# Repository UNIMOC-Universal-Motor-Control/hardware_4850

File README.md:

# hardware_4850
48V at 50A with optimised colling

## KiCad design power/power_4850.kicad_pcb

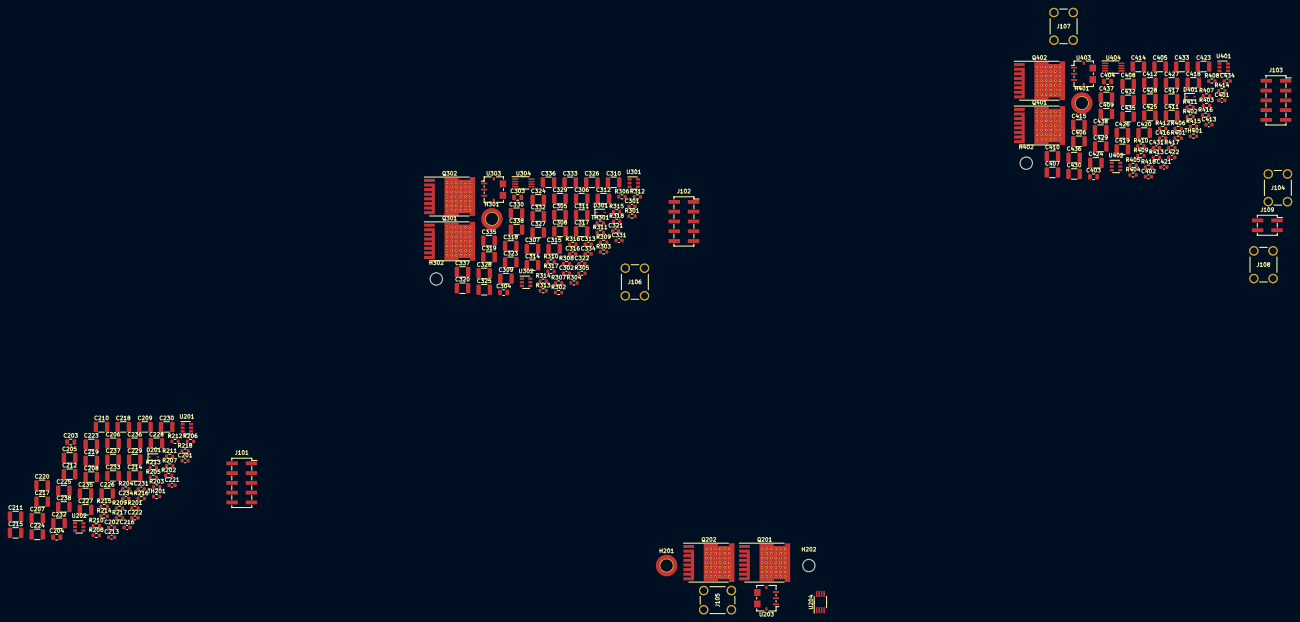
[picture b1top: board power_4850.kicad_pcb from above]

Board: 4 copper layers, 207 parts (0 on the bottom side), 92 nets, no tracks yet.

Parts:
C201, C202, C213, C216, C231, C234, C301, C302, C313, C316, C331, C334, C401, C402, C413, C416, C431, C434: 100n; C_0603_1608Metric
C203, C204, C303, C304, C403, C404: 10u; C_0805_2012Metric
C205, C206, C207, C208, C209, C210, C211, C212, C214, C215, C217, C218, C219, C220, C223, C224, C225, C226, C227, C228, C229, C230, C232, C233, C235, C236, C237, C238, C305, C306, C307, C308, C309, C310, C311, C312, C314, C315, C317, C318, C319, C320, C323, C324, C325, C326, C327, C328, C329, C330, C332, C333, C335, C336, C337, C338, C405, C406, C407, C408, C409, C410, C411, C412, C414, C415, C417, C418, C419, C420, C423, C424, C425, C426, C427, C428, C429, C430, C432, C433, C435, C436, C437, C438: 4u7; C_1210_3225Metric
C221, C222, C321, C322, C421, C422: DNP; C_0603_1608Metric
D201, D301, D401: 1N4148WS; D_SOD-323
H201, H301, H401: GND; MountingHole_3.2mm_M3_DIN965_Pad_TopOnly
H202, H302, H402: Phase; MountingHole_3.2mm_M3
J101: PA; PinSocket_2x05_P2.54mm_Vertical_SMD
J102: PB; PinSocket_2x05_P2.54mm_Vertical_SMD
J103: PC; PinSocket_2x05_P2.54mm_Vertical_SMD
J104: +; 8X8X8.4MM TERMINAL
J105: A; 8X8X8.4MM TERMINAL
J106: B; 8X8X8.4MM TERMINAL
J107: C; 8X8X8.4MM TERMINAL
J108: GND; 8X8X8.4MM TERMINAL
J109: Supply; PinSocket_2x02_P2.54mm_Vertical_SMD
Q201, Q202, Q301, Q302, Q401, Q402: IPT015N10N5; Infineon_PG-HSOF-8-1_ThermalVias
R201, R202, R203, R204, R211, R301, R302, R303, R304, R311, R401, R402, R403, R404, R411: 33k; R_0603_1608Metric
R205, R206, R207, R208, R305, R306, R307, R308, R405, R406, R407, R408: 1R; R_0603_1608Metric
R209, R210, R309, R310, R409, R410: 10R; R_0603_1608Metric
R212, R213, R214, R312, R313, R314, R412, R413, R414: 1k; R_0603_1608Metric
R215, R216, R315, R316, R415, R416: 4k7; R_0603_1608Metric
R217, R218, R317, R318, R417, R418: 10k; R_0603_1608Metric
TH201, TH301, TH401: NTC 10k; R_0603_1608Metric
U201, U202, U301, U302, U401, U402: 1EDN7550B; SOT-23-6
U203, U303, U403: ACS72981KLATR-150B5; Allegro_PSOF-7_4.8x6.4mm_P1.60mm
U204, U304, U404: MCP6D11-EMS; MSOP-8_3x3mm_P0.65mm

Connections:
+BATT: C205.1, C206.1, C207.1, C208.1, C209.1, C210.1, C211.1, C212.1, C214.1, C215.1, C217.1, C218.1, C219.1, C220.1, C223.1, C224.1, C225.1, C226.1, C227.1, C228.1, C229.1, C230.1, C232.1, C233.1, C235.1, C236.1, C237.1, C238.1, C305.1, C306.1, C307.1, C308.1, C309.1, C310.1, C311.1, C312.1, C314.1, C315.1, C317.1, C318.1, C319.1, C320.1, C323.1, C324.1, C325.1, C326.1, C327.1, C328.1, C329.1, C330.1, C332.1, C333.1, C335.1, C336.1, C337.1, C338.1, C405.1, C406.1, C407.1, C408.1, C409.1, C410.1, C411.1, C412.1, C414.1, C415.1, C417.1, C418.1, C419.1, C420.1, C423.1, C424.1, C425.1, C426.1, C427.1, C428.1, C429.1, C430.1, C432.1, C433.1, C435.1, C436.1, C437.1, C438.1, J104.1, J109.2, J109.4, Q201.3, Q301.3, Q401.3
/phase_a/+5V: C213.1, C231.1, J101.4, R213.1, U203.1, U204.3, U204.7
/phase_a/+12V: D201.2, J101.2, R210.2
/phase_a/GNDA: C213.2, C216.2, C231.2, C234.2, J101.6, R212.2, R214.2, U203.2, U203.4, U203.7, U204.6
/phase_a/I+: C222.1, J101.8, R218.1, U204.4
/phase_a/I-: C221.1, J101.10, R217.1, U204.5
/phase_a/Phase+: C201.2, C203.2, Q201.2, Q202.3, R211.1, U201.2, U203.5
/phase_a/Phase-: J105.1, U203.6
/phase_a/PwmH: J101.3, R201.2, R204.2
/phase_a/PwmL: J101.1, R202.2, R203.2
/phase_a/T+: J101.9, TH201.1
/phase_a/T-: J101.7, TH201.2
/phase_a/V: J101.5, R211.2, R212.1
/phase_b/+5V: C313.1, C331.1, J102.4, R313.1, U303.1, U304.3, U304.7
/phase_b/+12V: D301.2, J102.2, R310.2
/phase_b/GNDA: C313.2, C316.2, C331.2, C334.2, J102.6, R312.2, R314.2, U303.2, U303.4, U303.7, U304.6
/phase_b/I+: C322.1, J102.8, R318.1, U304.4
/phase_b/I-: C321.1, J102.10, R317.1, U304.5
/phase_b/Phase+: C301.2, C303.2, Q301.2, Q302.3, R311.1, U301.2, U303.5
/phase_b/Phase-: J106.1, U303.6
/phase_b/PwmH: J102.3, R301.2, R304.2
/phase_b/PwmL: J102.1, R302.2, R303.2
/phase_b/T+: J102.9, TH301.1
/phase_b/T-: J102.7, TH301.2
/phase_b/V: J102.5, R311.2, R312.1
/phase_c/+5V: C413.1, C431.1, J103.4, R413.1, U403.1, U404.3, U404.7
/phase_c/+12V: D401.2, J103.2, R410.2
/phase_c/GNDA: C413.2, C416.2, C431.2, C434.2, J103.6, R412.2, R414.2, U403.2, U403.4, U403.7, U404.6
/phase_c/I+: C422.1, J103.8, R418.1, U404.4
/phase_c/I-: C421.1, J103.10, R417.1, U404.5
/phase_c/Phase+: C401.2, C403.2, Q401.2, Q402.3, R411.1, U401.2, U403.5
/phase_c/Phase-: J107.1, U403.6
/phase_c/PwmH: J103.3, R401.2, R404.2
/phase_c/PwmL: J103.1, R402.2, R403.2
/phase_c/T+: J103.9, TH401.1
/phase_c/T-: J103.7, TH401.2
/phase_c/V: J103.5, R411.2, R412.1
GNDPWR: C202.2, C204.2, C205.2, C206.2, C207.2, C208.2, C209.2, C210.2, C211.2, C212.2, C214.2, C215.2, C217.2, C218.2, C219.2, C220.2, C223.2, C224.2, C225.2, C226.2, C227.2, C228.2, C229.2, C230.2, C232.2, C233.2, C235.2, C236.2, C237.2, C238.2, C302.2, C304.2, C305.2, C306.2, C307.2, C308.2, C309.2, C310.2, C311.2, C312.2, C314.2, C315.2, C317.2, C318.2, C319.2, C320.2, C323.2, C324.2, C325.2, C326.2, C327.2, C328.2, C329.2, C330.2, C332.2, C333.2, C335.2, C336.2, C337.2, C338.2, C402.2, C404.2, C405.2, C406.2, C407.2, C408.2, C409.2, C410.2, C411.2, C412.2, C414.2, C415.2, C417.2, C418.2, C419.2, C420.2, C423.2, C424.2, C425.2, C426.2, C427.2, C428.2, C429.2, C430.2, C432.2, C433.2, C435.2, C436.2, C437.2, C438.2, H201.1, H301.1, H401.1, J108.1, J109.1, J109.3, Q202.2, Q302.2, Q402.2, U202.2, U302.2, U402.2
unnamed: C201.1, C203.1, R209.1, U201.4
unnamed: C202.1, C204.1, R210.1, U202.4
unnamed: C216.1, R213.2, R214.1, R216.2
unnamed: C221.2, R215.1, R217.2, U204.8
unnamed: C222.2, R216.1, R218.2, U204.1
unnamed: C234.1, U204.2
unnamed: C301.1, C303.1, R309.1, U301.4
unnamed: C302.1, C304.1, R310.1, U302.4
unnamed: C316.1, R313.2, R314.1, R316.2
unnamed: C321.2, R315.1, R317.2, U304.8
unnamed: C322.2, R316.1, R318.2, U304.1
unnamed: C334.1, U304.2
unnamed: C401.1, C403.1, R409.1, U401.4
unnamed: C402.1, C404.1, R410.1, U402.4
unnamed: C416.1, R413.2, R414.1, R416.2
unnamed: C421.2, R415.1, R417.2, U404.8
unnamed: C422.2, R416.1, R418.2, U404.1
unnamed: C434.1, U404.2
unnamed: D201.1, R209.2
unnamed: D301.1, R309.2
unnamed: D401.1, R409.2
unnamed: Q201.1, R205.1, R206.1
unnamed: Q202.1, R207.1, R208.1
unnamed: Q301.1, R305.1, R306.1
unnamed: Q302.1, R307.1, R308.1
unnamed: Q401.1, R405.1, R406.1
unnamed: Q402.1, R407.1, R408.1
unnamed: R201.1, U201.3
unnamed: R202.1, U201.1
unnamed: R203.1, U202.3
unnamed: R204.1, U202.1
unnamed: R205.2, U201.5
unnamed: R206.2, U201.6
unnamed: R207.2, U202.5
unnamed: R208.2, U202.6
unnamed: R215.2, U203.3
unnamed: R301.1, U301.3
unnamed: R302.1, U301.1
unnamed: R303.1, U302.3
unnamed: R304.1, U302.1
unnamed: R305.2, U301.5
unnamed: R306.2, U301.6
unnamed: R307.2, U302.5
unnamed: R308.2, U302.6
unnamed: R315.2, U303.3
unnamed: R401.1, U401.3
unnamed: R402.1, U401.1
unnamed: R403.1, U402.3
unnamed: R404.1, U402.1
unnamed: R405.2, U401.5
unnamed: R406.2, U401.6
unnamed: R407.2, U402.5
unnamed: R408.2, U402.6
unnamed: R415.2, U403.3

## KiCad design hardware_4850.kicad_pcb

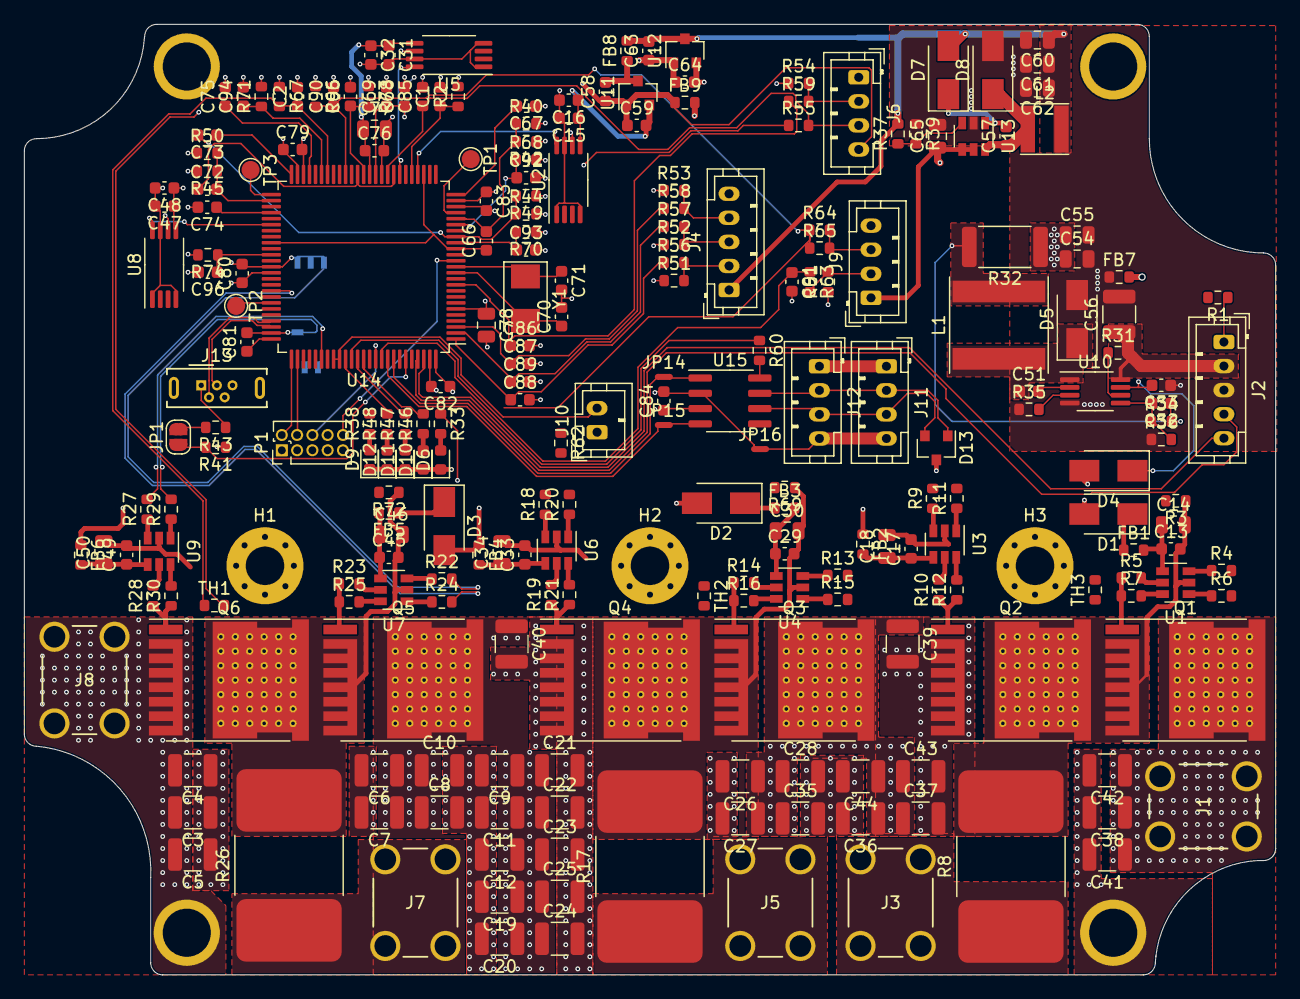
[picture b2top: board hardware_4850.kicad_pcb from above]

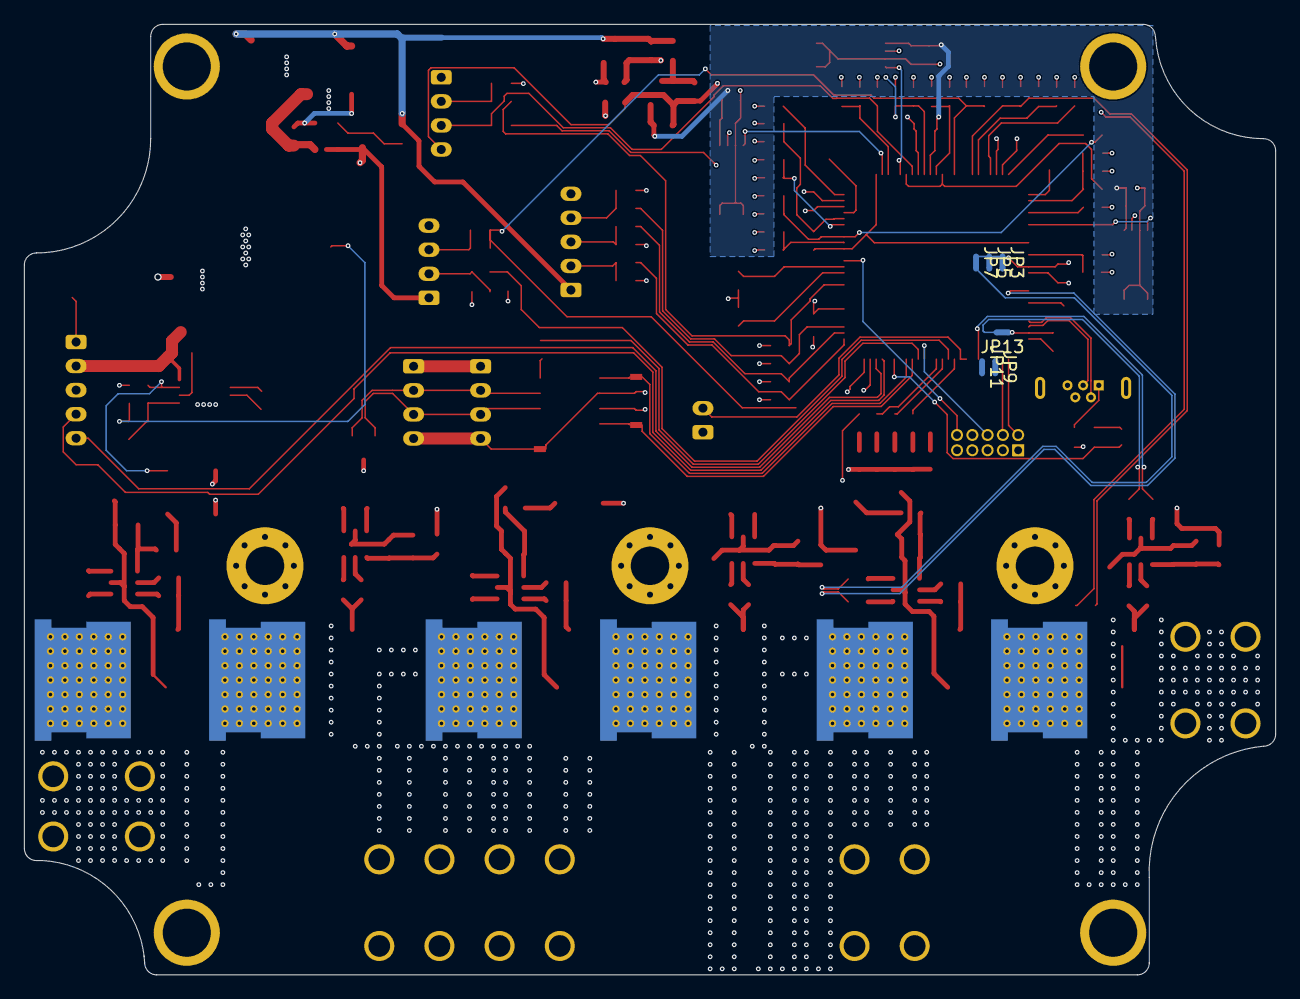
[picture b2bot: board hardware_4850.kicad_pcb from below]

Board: 4 copper layers, 104.0 x 79.0 mm, 250 parts (6 on the bottom side), 146 nets.

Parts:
C1, C2, C13, C16, C17, C29, C32, C33, C45, C48, C49, C51, C57, C67, C68, C74, C75, C76, C79, C80, C81, C82, C83, C84, C85, C92, C93, C94, C95, C96: 100n; C_0603_1608Metric
C3, C4, C5, C6, C7, C8, C9, C10, C11, C12, C19, C20, C21, C22, C23, C24, C25, C26, C27, C28, C35, C36, C37, C38, C39, C40, C41, C42, C43, C44, C56: 4u7; C_1210_3225Metric
C14, C18, C30, C34, C46, C50, C54, C55, C60, C61, C62, C65, C77, C78: 10u; C_0805_2012Metric
C15, C31, C47, C66, C72, C73: 10n; C_0603_1608Metric
C52, C86, C87, C88, C89, C90, C91: 2n2; C_0603_1608Metric
C53, C58, C59, C63, C64, C69: 1u; C_0603_1608Metric
C70, C71: 15p; C_0603_1608Metric
D1, D2, D3, D4, D5, D7, D8: SS210; D_SMA
D6: 12V; LED_0603_1608Metric
D9: 3V3; LED_0603_1608Metric
D10: RUN; LED_0603_1608Metric
D11: ERROR; LED_0603_1608Metric
D12: PWM; LED_0603_1608Metric
D13: ESDCAN24-2BLY; SOT-23
FB1, FB2, FB3, FB4, FB5, FB6, FB7, FB8, FB9: BLM18PG221SN1D; R_0603_1608Metric
H1, H2, H3: MountingHole_Pad; MountingHole_3.2mm_M3_Pad_Via
J1: +; 8X8X8.4MM TERMINAL
J2: Display; JST_PH_B5B-PH-K_1x05_P2.00mm_Vertical
J3: A; 8X8X8.4MM TERMINAL
J4: HALL; JST_PH_B5B-PH-K_1x05_P2.00mm_Vertical
J5: B; 8X8X8.4MM TERMINAL
J6: MOT_AUX; JST_PH_B4B-PH-K_1x04_P2.00mm_Vertical
J7: C; 8X8X8.4MM TERMINAL
J8: GND; 8X8X8.4MM TERMINAL
J9: CRANK; JST_PH_B4B-PH-K_1x04_P2.00mm_Vertical
J10: Enable; JST_PH_B2B-PH-K_1x02_P2.00mm_Vertical
J11: CAN_IN; JST_PH_B4B-PH-K_1x04_P2.00mm_Vertical
J12: CAN_OUT; JST_PH_B4B-PH-K_1x04_P2.00mm_Vertical
J13: Debug; USB_Micro-B_Wuerth_614105150721_Vertical
JP1: BTLDR; SolderJumper-2_P1.3mm_Open_RoundedPad1.0x1.5mm
JP3: PA-; NetTie-2_SMD_Pad0.5mm
JP5: PB-; NetTie-2_SMD_Pad0.5mm
JP7: PC-; NetTie-2_SMD_Pad0.5mm
JP9: PAN-; NetTie-2_SMD_Pad0.5mm
JP11: PBN-; NetTie-2_SMD_Pad0.5mm
JP13: PCN-; NetTie-2_SMD_Pad0.5mm
JP14: CAN_TX; NetTie-2_SMD_Pad0.5mm
JP15: CAN_RX; NetTie-2_SMD_Pad0.5mm
JP16: CAN_GND; NetTie-2_SMD_Pad0.5mm
L1: 330u; L_Taiyo-Yuden_NR-80xx
L2: 10u; L_Taiyo-Yuden_NR-40xx
N1: Housing; RND-455-00370
P1: SWD; PinHeader_2x05_P1.27mm_Vertical
Q1, Q2, Q3, Q4, Q5, Q6: IPT015N10N5; Infineon_PG-HSOF-8-1_ThermalVias
R1, R3, R4, R6, R9, R11, R13, R15, R18, R20, R22, R24, R27, R29, R69, R72: 33k; R_0603_1608Metric
R2, R40, R42, R44, R45, R49, R50, R51, R52, R53, R54, R61, R62, R68, R71, R74: 1k; R_0603_1608Metric
R5, R7, R10, R12, R14, R16, R19, R21, R23, R25, R28, R30: 1R; R_0603_1608Metric
R8, R17, R26: R0002; R_5930_15076Metric_Pad5.20x8.75mm
R31: 220k; R_0603_1608Metric
R32: 2R2; R_2512_6332Metric
R33, R36, R43, R56, R57, R58, R59, R63, R64, R65, R66: 3k3; R_0603_1608Metric
R34, R39, R41, R55, R60, R67, R70, R73: 10k; R_0603_1608Metric
R35: 100k; R_0603_1608Metric
R37: 56k; R_0603_1608Metric
R38, R46, R47, R48: 470R; R_0603_1608Metric
TH1, TH2, TH3: NTC 10k; R_0603_1608Metric
TP1: IA_AC; TestPoint_Pad_D1.5mm
TP2: IC_AC; TestPoint_Pad_D1.5mm
TP3: IB_AC; TestPoint_Pad_D1.5mm
U1, U3, U4, U6, U7, U9: 1EDN7550B; SOT-23-6
U2, U5, U8: INA240A2PWR; TSSOP-8_4.4x3mm_P0.65mm
U10: LM5008; MSOP-8_3x3mm_P0.65mm
U11, U12: XC6206P332MR; SOT-23
U13: LMR12010X; SOT-23-6
U14: STM32G473VCTx; LQFP-100_14x14mm_P0.5mm
U15: SN65HVD230; SOIC-8_3.9x4.9mm_P1.27mm
Y1: 8MHz; Crystal_SMD_5032-2Pin_5.0x3.2mm

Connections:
+3.3VADC: C15.1, C16.1, C31.1, C32.1, C47.1, C48.1, C59.2, C76.1, C77.1, U2.5, U5.5, U8.5, U11.2, U14.37
+3V3: C64.2, C78.1, C79.1, C80.1, C81.1, C82.1, C83.1, C84.1, P1.1, R38.2, R51.1, R52.1, R53.1, R54.1, R61.1, R62.2, U12.2, U14.6, U14.24, U14.49, U14.64, U14.75, U14.100, U15.3
+5V: C60.1, C61.1, C62.1, C63.2, D7.2, FB8.2, J4.1, L2.2, R37.2, U12.3
+12V: C54.1, C55.1, C65.1, D1.2, D2.2, D3.2, D4.2, FB2.1, FB4.1, FB6.1, J9.1, R32.1, R33.1, U13.4, U13.5
+BATT: C3.1, C4.1, C5.1, C6.1, C7.1, C8.1, C9.1, C10.1, C11.1, C12.1, C19.1, C20.1, C21.1, C22.1, C23.1, C24.1, C25.1, C26.1, C27.1, C28.1, C35.1, C36.1, C37.1, C38.1, C39.1, C40.1, C41.1, C42.1, C43.1, C44.1, J1.1, J2.1, Q1.3, Q3.3, Q5.3, R1.1
/Interface/CAN+: D13.1, J11.2, J12.2, U15.7
/Interface/CAN-: D13.2, J11.3, J12.3, U15.6
/Interface/CAN_GND: J11.4, J12.4, JP16.2
/Interface/CAN_RX: JP15.1, U14.92
/Interface/CAN_SLP: R60.1, U14.91
/Interface/CAN_TX: JP14.1, U14.93
/Interface/ENABLE+: J10.1, R62.1
/Interface/ENABLE-: J10.2, U14.83, U14.84
/Interface/HALL_A: C88.1, R56.1, U14.1
/Interface/HALL_A_IN: J4.2, R51.2, R56.2
/Interface/HALL_B: C89.1, R57.1, U14.2
/Interface/HALL_B_IN: J4.3, R52.2, R57.2
/Interface/HALL_C: C87.1, R58.1, U14.3
/Interface/HALL_C_IN: J4.4, R53.2, R58.2
/Interface/PULSE_CRK: C91.1, R63.1, U14.86
/Interface/PULSE_CRK_IN: J9.2, R61.2, R63.2
/Interface/PULSE_MOT: C86.1, R59.1, U14.10
/Interface/PULSE_MOT_IN: J6.2, R54.2, R59.2
/Interface/TORQ_CRK_IN: J9.3, R64.2, R65.2
/Interface/VREF: C68.1, C69.1, R40.2, R44.2, R45.2, R55.1, R67.1, R70.1, R73.1, U2.6, U5.6, U8.6, U14.36
/mcu/AIN_CRK_TORQ: C90.1, R64.1, R65.1, R66.2, U14.41
/mcu/AIN_IA: U2.8, U14.29
/mcu/AIN_IB: U5.8, U14.32
/mcu/AIN_IC: U8.8, U14.56
/mcu/AIN_TEMP_A: C2.1, R67.2, TH1.1, U14.44
/mcu/AIN_TEMP_B: C93.1, R70.2, TH2.1, U14.17
/mcu/AIN_TEMP_C: C95.1, R73.2, TH3.1, U14.38
/mcu/AIN_TEMP_MOT: C85.1, J6.3, R55.2, U14.34
/mcu/AIN_VA: C92.1, R3.2, R68.1, U14.20
/mcu/AIN_VB: C94.1, R69.2, R71.1, U14.45
/mcu/AIN_VC: C96.1, R72.2, R74.1, U14.61
/mcu/AIN_VDC: C1.1, R1.2, R2.1, U14.30
/mcu/DISP_RX: J2.5, U14.98
/mcu/DISP_TX: J2.4, U14.97
/mcu/IA_AC: TP1.1, U14.22
/mcu/IA_AC_BIAS: C67.2, U14.25
/mcu/IA_AC_IN: C66.2, R40.1, R42.2, U14.21
/mcu/IA_DC: C66.1, U14.16, U14.28, U14.59
/mcu/IB_AC: TP3.1, U14.51
/mcu/IB_AC_BIAS: C75.1, U14.47
/mcu/IB_AC_IN: C72.2, R45.1, R50.2, U14.52
/mcu/IB_DC: C72.1, U14.33, U14.39
/mcu/IC_AC: TP2.1, U14.69
/mcu/IC_AC_BIAS: C74.1, U14.54
/mcu/IC_AC_IN: C73.2, R44.1, R49.2, U14.18
/mcu/IC_DC: C73.1, U14.50
/mcu/NRST: P1.10, U14.14
/mcu/PWM_A+: R6.2, U14.65
/mcu/PWM_A-: JP3.2, R4.2
/mcu/PWM_AN+: R9.2, U14.79
/mcu/PWM_AN-: JP9.2, R11.2
/mcu/PWM_B+: R15.2, U14.66
/mcu/PWM_B-: JP5.2, R13.2
/mcu/PWM_BN+: R18.2, U14.80
/mcu/PWM_BN-: JP11.2, R20.2
/mcu/PWM_C+: R24.2, U14.67
/mcu/PWM_C-: JP7.2, R22.2
/mcu/PWM_CN+: R27.2, U14.81
/mcu/PWM_CN-: JP13.2, R29.2
/mcu/SWD_CLK: P1.4, U14.77
/mcu/SWD_IO: P1.2, U14.76
/mcu/SWD_SWO: P1.6, U14.90
/mcu/USB_D+: J13.3, U14.73
/mcu/USB_D-: J13.2, U14.72
/mcu/USB_VBUS: JP1.2, R43.2
/phase_a/Phase+: J3.1, R8.1, U2.2
/phase_a/Phase-: C13.2, C14.2, Q1.2, Q2.3, R3.1, R8.2, U1.2, U2.3
/phase_b/Phase+: J5.1, R17.1, U5.2
/phase_b/Phase-: C29.2, C30.2, Q3.2, Q4.3, R17.2, R69.1, U4.2, U5.3
/phase_c/Phase+: J7.1, R26.1, U8.2
/phase_c/Phase-: C45.2, C46.2, Q5.2, Q6.3, R26.2, R72.1, U7.2, U8.3
/power_supply/DCDC_VIN: C56.1, J2.2, R31.2, U10.8
GNDA: C1.2, C2.2, C15.2, C16.2, C31.2, C32.2, C47.2, C48.2, C58.1, C59.1, C67.1, C68.2, C69.2, C74.2, C75.2, C76.2, C77.2, C85.2, C90.2, C92.2, C93.2, C94.2, C95.2, C96.2, FB9.1, J6.4, R2.2, R42.1, R49.1, R50.1, R66.1, R68.2, R71.2, R74.2, TH1.2, TH2.2, TH3.2, U2.1, U2.4, U2.7, U5.1, U5.4, U5.7, U8.1, U8.4, U8.7, U11.1, U14.35
GNDD: C53.1, C54.2, C55.2, C56.2, C60.2, C61.2, C62.2, C63.1, C64.1, C65.2, C70.2, C71.2, C78.2, C79.2, C80.2, C81.2, C82.2, C83.2, C84.2, C86.2, C87.2, C88.2, C89.2, C91.2, D5.2, D6.1, D8.2, D9.1, D10.1, D11.1, D12.1, D13.3, FB7.1, FB9.2, J2.3, J4.5, J6.1, J9.4, J13.5, J13.6, JP3.1, JP5.1, JP7.1, JP9.1, JP11.1, JP13.1, JP16.1, P1.3, P1.5, R35.1, R36.1, R39.1, R41.1, U10.4, U12.1, U13.2, U14.23, U14.48, U14.63, U14.74, U14.99, U15.2
GNDPWR: C3.2, C4.2, C5.2, C6.2, C7.2, C8.2, C9.2, C10.2, C11.2, C12.2, C17.2, C18.2, C19.2, C20.2, C21.2, C22.2, C23.2, C24.2, C25.2, C26.2, C27.2, C28.2, C33.2, C34.2, C35.2, C36.2, C37.2, C38.2, C39.2, C40.2, C41.2, C42.2, C43.2, C44.2, C49.2, C50.2, FB7.2, H1.1, H2.1, H3.1, J8.1, N1.1, Q2.2, Q4.2, Q6.2, U3.2, U6.2, U9.2
unnamed: C13.1, C14.1, FB1.2, U1.4
unnamed: C17.1, C18.1, FB2.2, U3.4
unnamed: C29.1, C30.1, FB3.2, U4.4
unnamed: C33.1, C34.1, FB4.2, U6.4
unnamed: C45.1, C46.1, FB5.2, U7.4
unnamed: C49.1, C50.1, FB6.2, U9.4
unnamed: C51.1, D5.1, L1.1, U10.1
unnamed: C51.2, U10.2
unnamed: C52.1, L1.2, R32.2, R34.2
unnamed: C52.2, R34.1, R36.2, U10.5
unnamed: C53.2, D4.1, U10.7
unnamed: C57.1, D8.1, L2.1, U13.6
unnamed: C57.2, D7.1, U13.1
unnamed: C58.2, FB8.1, U11.3
unnamed: C70.1, U14.12, Y1.2
unnamed: C71.1, U14.13, Y1.1
unnamed: D1.1, FB1.1
unnamed: D2.1, FB3.1
unnamed: D3.1, FB5.1
unnamed: D6.2, R33.2
unnamed: D9.2, R38.1
unnamed: D10.2, R46.1
unnamed: D11.2, R47.1
unnamed: D12.2, R48.1
unnamed: J11.1, J12.1
unnamed: J13.1, R43.1
unnamed: JP1.1, R41.2, U14.95
unnamed: JP14.2, U15.1
unnamed: JP15.2, U15.4
unnamed: Q1.1, R5.1, R7.1
unnamed: Q2.1, R10.1, R12.1
unnamed: Q3.1, R14.1, R16.1
unnamed: Q4.1, R19.1, R21.1
unnamed: Q5.1, R23.1, R25.1
unnamed: Q6.1, R28.1, R30.1
unnamed: R4.1, U1.3
unnamed: R5.2, U1.5
unnamed: R6.1, U1.1
unnamed: R7.2, U1.6
unnamed: R9.1, U3.3
unnamed: R10.2, U3.5
unnamed: R11.1, U3.1
unnamed: R12.2, U3.6
unnamed: R13.1, U4.3
unnamed: R14.2, U4.5
unnamed: R15.1, U4.1
unnamed: R16.2, U4.6
unnamed: R18.1, U6.3
unnamed: R19.2, U6.5
unnamed: R20.1, U6.1
unnamed: R21.2, U6.6
unnamed: R22.1, U7.3
unnamed: R23.2, U7.5
unnamed: R24.1, U7.1
unnamed: R25.2, U7.6
unnamed: R27.1, U9.3
unnamed: R28.2, U9.5
unnamed: R29.1, U9.1
unnamed: R30.2, U9.6
unnamed: R31.1, U10.6
unnamed: R35.2, U10.3
unnamed: R37.1, R39.2, U13.3
unnamed: R46.2, U14.88
unnamed: R47.2, U14.87
unnamed: R48.2, U14.85
unnamed: R60.2, U15.8

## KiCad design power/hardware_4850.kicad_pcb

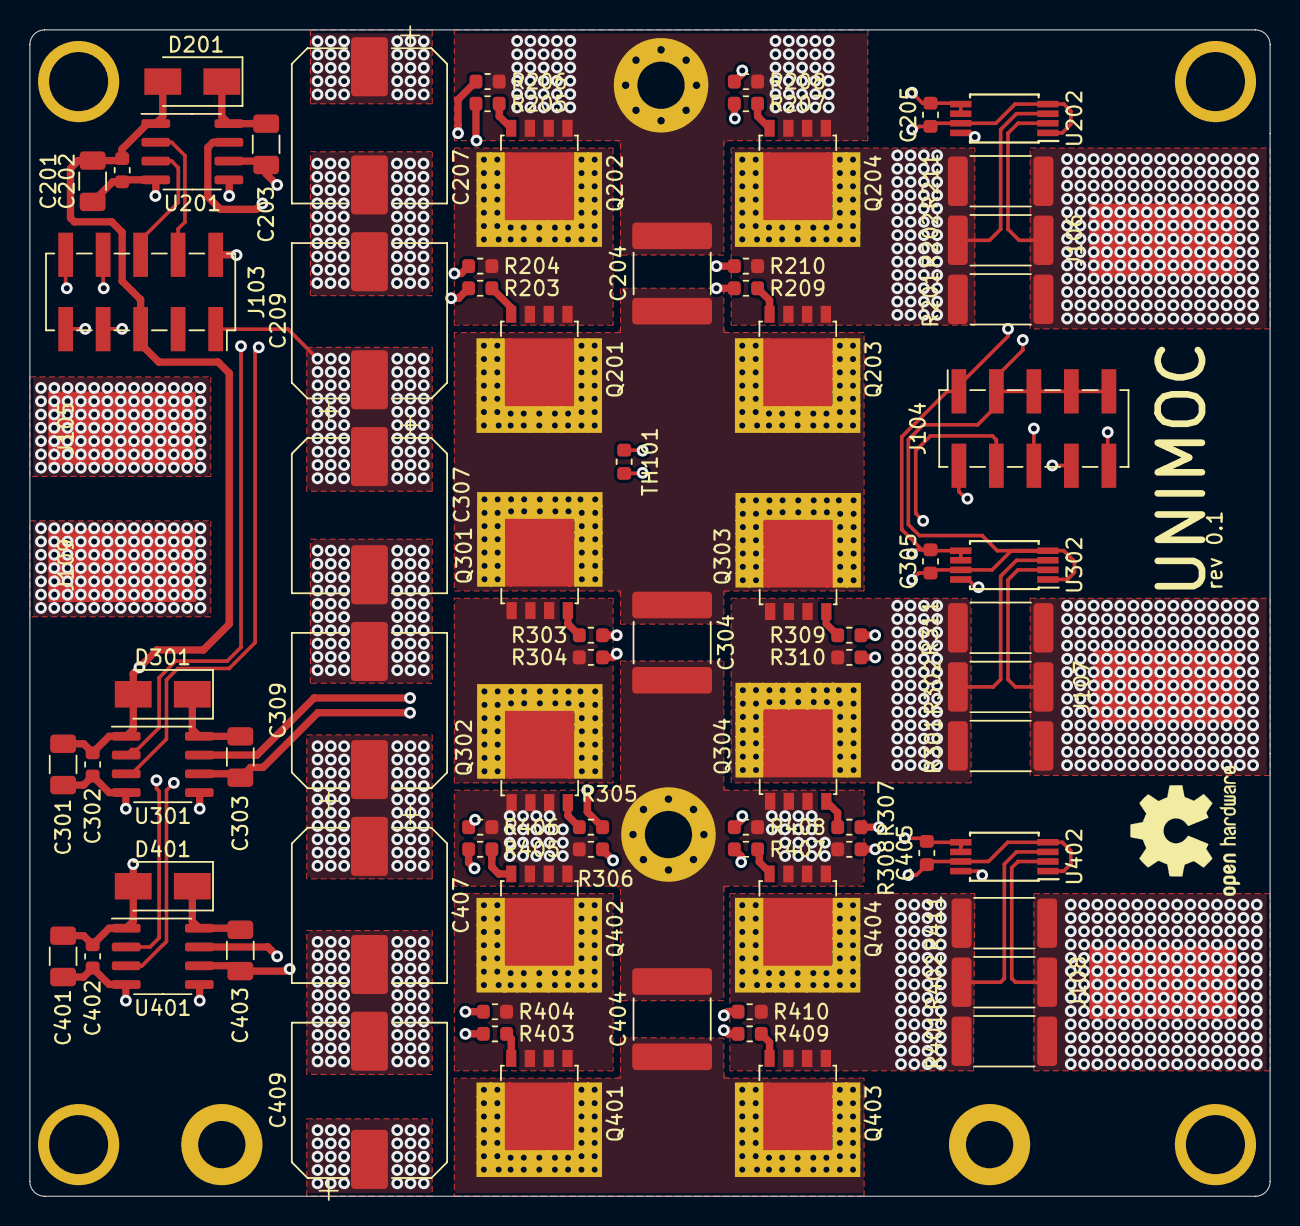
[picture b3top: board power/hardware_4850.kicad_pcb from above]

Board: 4 copper layers, 84.0 x 79.0 mm, 88 parts (0 on the bottom side), 49 nets.

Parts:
C201, C203, C301, C303, C401, C403: 10u; C_1206_3216Metric
C202, C205, C302, C305, C402, C405: 100n; C_0603_1608Metric
C204, C304, C404: 10u; C_2220_5650Metric
C207, C209, C307, C309, C407, C409: 56u; CP_Elec_10x10
D201, D301, D401: SS110R3G; D_SMA
H104, H107: GND; MountingHole_3.2mm_M3_ISO14580_Pad
H105, H106: GND; MountingHole_3.2mm_M3_Pad_Via
J103: PWM; PinSocket_2x05_P2.54mm_Vertical_SMD
J104: ADC; PinSocket_2x05_P2.54mm_Vertical_SMD
J105: +; SolderWirePad_1x01_SMD_5x10mm
J106: A; SolderWirePad_1x01_SMD_5x10mm
J107: B; SolderWirePad_1x01_SMD_5x10mm
J108: C; SolderWirePad_1x01_SMD_5x10mm
J109: GND; SolderWirePad_1x01_SMD_5x10mm
N101: Housing_Pad; RND-455-00370
Q201, Q202, Q203, Q204, Q301, Q302, Q303, Q304, Q401, Q402, Q403, Q404: NCEP6080AG; LFPAK56_ThermalVias-1
R201, R202, R211, R301, R302, R311, R401, R402, R411: 2mR; R_2512_6332Metric
R203, R204, R205, R206, R207, R208, R209, R210, R303, R304, R305, R306, R307, R308, R309, R310, R403, R404, R405, R406, R407, R408, R409, R410: 1R1; R_0603_1608Metric
TH101: NTC 10k; R_0603_1608Metric
U201, U301, U401: LM5109BMA; SOIC-8_3.9x4.9mm_P1.27mm
U202, U302, U402: INA240A1PWR; TSSOP-8_4.4x3mm_P0.65mm

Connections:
+3.3VA: C205.1, C305.1, C405.1, J104.1, U202.5, U202.6, U302.5, U302.6, U402.5, U402.6
+12P: C201.1, C202.1, C301.1, C302.1, C401.1, C402.1, D201.2, D301.2, D401.2, J103.5, U201.1, U301.1, U401.1
+BATT: C204.1, C207.1, C209.1, C304.1, C307.1, C309.1, C404.1, C407.1, C409.1, J103.1, J105.1, Q201.5, Q203.5, Q301.5, Q303.5, Q401.5, Q403.5
/phase_a/I: J104.6, U202.8
/phase_a/Phase: J106.1, R201.1, R202.1, R211.1, U202.2
/phase_a/PwmH: J103.4, U201.2
/phase_a/PwmL: J103.6, U201.3
/phase_b/I: J104.4, U302.8
/phase_b/Phase: J107.1, R301.1, R302.1, R311.1, U302.2
/phase_b/PwmH: J103.8, U301.2
/phase_b/PwmL: J103.10, U301.3
/phase_c/I: J104.2, U402.8
/phase_c/Phase: J108.1, R401.1, R402.1, R411.1, U402.2
/phase_c/PwmH: J103.9, U401.2
/phase_c/PwmL: J103.7, U401.3
GND: C205.2, C305.2, C405.2, J104.3, J104.5, J104.7, J104.9, U202.1, U202.4, U202.7, U302.1, U302.4, U302.7, U402.1, U402.4, U402.7
GNDPWR: C204.2, C207.2, C209.2, C304.2, C307.2, C309.2, C404.2, C407.2, C409.2, H104.1, H105.1, H106.1, H107.1, J103.2, J109.1, N101.1, Q202.1, Q202.2, Q202.3, Q204.1, Q204.2, Q204.3, Q302.1, Q302.2, Q302.3, Q304.1, Q304.2, Q304.3, Q402.1, Q402.2, Q402.3, Q404.1, Q404.2, Q404.3, R206.1, R208.1, R306.1, R308.1, R406.1, R408.1
unnamed: C201.2, C202.2, R206.2, R208.2, U201.4
unnamed: C203.1, D201.1, U201.8
unnamed: C203.2, R204.2, R210.2, U201.6
unnamed: C301.2, C302.2, R306.2, R308.2, U301.4
unnamed: C303.1, D301.1, U301.8
unnamed: C303.2, R304.2, R310.2, U301.6
unnamed: C401.2, C402.2, R406.2, R408.2, U401.4
unnamed: C403.1, D401.1, U401.8
unnamed: C403.2, R404.2, R410.2, U401.6
unnamed: J104.8, TH101.1
unnamed: J104.10, TH101.2
unnamed: Q201.1, Q201.2, Q201.3, Q202.5, Q203.1, Q203.2, Q203.3, Q204.5, R201.2, R202.2, R204.1, R210.1, R211.2, U202.3
unnamed: Q201.4, R203.1
unnamed: Q202.4, R205.1
unnamed: Q203.4, R209.1
unnamed: Q204.4, R207.1
unnamed: Q301.1, Q301.2, Q301.3, Q302.5, Q303.1, Q303.2, Q303.3, Q304.5, R301.2, R302.2, R304.1, R310.1, R311.2, U302.3
unnamed: Q301.4, R303.1
unnamed: Q302.4, R305.1
unnamed: Q303.4, R309.1
unnamed: Q304.4, R307.1
unnamed: Q401.1, Q401.2, Q401.3, Q402.5, Q403.1, Q403.2, Q403.3, Q404.5, R401.2, R402.2, R404.1, R410.1, R411.2, U402.3
unnamed: Q401.4, R403.1
unnamed: Q402.4, R405.1
unnamed: Q403.4, R409.1
unnamed: Q404.4, R407.1
unnamed: R203.2, R209.2, U201.7
unnamed: R205.2, R207.2, U201.5
unnamed: R303.2, R309.2, U301.7
unnamed: R305.2, R307.2, U301.5
unnamed: R403.2, R409.2, U401.7
unnamed: R405.2, R407.2, U401.5

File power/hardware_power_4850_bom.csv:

Reference, Quantity, Value, Footprint, Datasheet, Part#
C202 C205 C302 C305 C402 C405 ,6,"100n","Capacitor_SMD:C_0603_1608Metric","~","CL10B104KBNC"
C203 C201 C303 C301 C403 C401 ,6,"10u","Capacitor_SMD:C_1206_3216Metric","~","CC1206ZKY5V8BB106"
C204 C304 C404 ,3,"10u","Capacitor_SMD:C_2220_5650Metric","~","FS55X106K101EHG"
C207 C209 C307 C309 C407 C409 ,6,"56u","Capacitor_SMD:CP_Elec_10x10","~","GYA1J560MCQ1GS"
D201 D301 D401 ,3,"SS110R3G","Diode_SMD:D_SMA","","SS110R3G"
H104 H107 ,2,"GND","MountingHole:MountingHole_3.2mm_M3_ISO14580_Pad","~"
H106 H105 ,2,"GND","MountingHole:MountingHole_3.2mm_M3_Pad_Via","~"
J103 ,1,"PWM","Connector_PinSocket_2.54mm:PinSocket_2x05_P2.54mm_Vertical_SMD","~","C261072"
J104 ,1,"ADC","Connector_PinSocket_2.54mm:PinSocket_2x05_P2.54mm_Vertical_SMD","~","C261072"
J105 ,1,"+","Connector_Wire:SolderWirePad_1x01_SMD_5x10mm","~"
J106 ,1,"A","Connector_Wire:SolderWirePad_1x01_SMD_5x10mm","~"
J107 ,1,"B","Connector_Wire:SolderWirePad_1x01_SMD_5x10mm","~"
J108 ,1,"C","Connector_Wire:SolderWirePad_1x01_SMD_5x10mm","~"
J109 ,1,"GND","Connector_Wire:SolderWirePad_1x01_SMD_5x10mm","~"
N101 ,1,"Housing_Pad","hardware_4850:RND-455-00370","~","RND 455-00370"
Q201 Q203 Q202 Q204 Q301 Q303 Q302 Q304 Q401 Q403 Q402 Q404 ,12,"NCEP6080AG","Package_TO_SOT_SMD:LFPAK56_ThermalVias-1","","NCEP6080AG"
R201 R202 R211 R301 R302 R311 R401 R402 R411 ,9,"2mR","Resistor_SMD:R_2512_6332Metric","~","MS122WF200NT4E"
R203 R209 R207 R205 R206 R208 R204 R210 R303 R309 R307 R305 R306 R308 R304 R310 R403 R409 R407 R405 R406 R408 R404 R410 ,24,"1R1","Resistor_SMD:R_0603_1608Metric","~","MCR03ERTJ1R1"
TH101 ,1,"NTC 10k","Resistor_SMD:R_0603_1608Metric","~","NCP18XH103F03RB"
U201 U301 U401 ,3,"LM5109BMA","Package_SO:SOIC-8_3.9x4.9mm_P1.27mm","http://www.ti.com/lit/ds/symlink/lm5109b.pdf","LM5109BMAX/NOPB"
U202 U302 U402 ,3,"INA240A1PWR","Package_SO:TSSOP-8_4.4x3mm_P0.65mm","http://www.ti.com/lit/ds/symlink/ina240.pdf","595-INA240A2PWR"
